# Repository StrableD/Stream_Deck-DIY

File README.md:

# Stream_Deck-DIY

Ich habe mir vorgenommen ein Stream Deck mit 15 Tasten selber zu bauen.
In diesem Repository will ich meine Reise dokumentieren und damit auch eine Anleitung für andere geben.

---

**Annotation:** For the English version, check [this section](#english-version).

## Ziele

- selbstgebautes Stream Deck mit 15 Tasten
- kompatibel mit Stream Deck Software und Alternativen
- günstiger als das Original

## Aktueller Stand

Aktuell sind wir in der Planungsphase.

Für weitere Informationen zur Planung und zukünftige Umsetzung schau dir die Dateien, welche in der [folgenden Sektion](#dateien) beschrieben werden, an.

## Dateien

Aufgeteilt sind die Dateien in Deutsch ([`de` Ordner](./de/)) und Englisch ([`en` Ordner](#english-version)).
Hierbei sind sie gleich benannt, damit man sie einfach vergleichen kann.

Hierbei gibt es folgende Dateien:

- `README.md`: Diese Datei, mit einer Übersicht über das Projekt ([englische Version](#english-version) in `en/README.md`)
- `planned.md`: Geplante Funktionen, Bauteile, Schaltplan, Aufbau
- `roadmap.md`: Geplanter Zeitplan für die Umsetzung
- `stream_deck-circuit`: Das KiCad Projekt mit Schaltplan und PCB-Layout

## English version

There is a english translation planned.
It can be found in the `en` folder.

## Credits

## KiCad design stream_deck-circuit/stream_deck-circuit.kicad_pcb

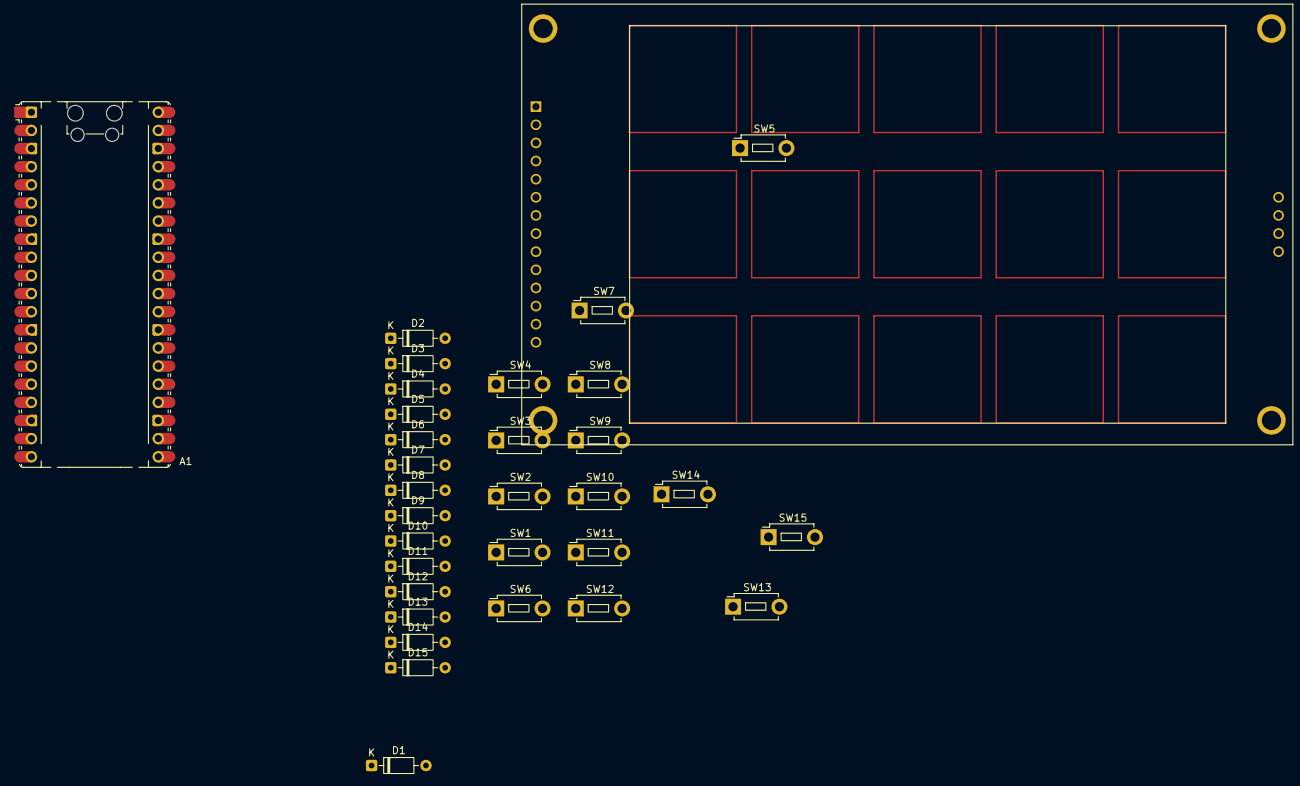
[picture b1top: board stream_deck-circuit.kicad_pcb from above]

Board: 2 copper layers, 32 parts (0 on the bottom side), 29 nets, no tracks yet.

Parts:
A1: RaspberryPi_Pico; RaspberryPi_Pico_Common_Unspecified
D1, D2, D3, D4, D5, D6, D7, D8, D9, D10, D11, D12, D13, D14, D15: 1N4148; D_DO-35_SOD27_P7.62mm_Horizontal
ST1: CR2019-MI5027
SW1, SW2, SW3, SW4, SW5, SW6, SW7, SW8, SW9, SW10, SW11, SW12, SW13, SW14, SW15: SW_MEC_5G; SW_PUSH_1P1T_6x3.5mm_H5.0_APEM_MJTP1250

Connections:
unnamed: A1.36 (3V3), ST1.1 (VCC)
unnamed: A1.5 (GPIO3), D1.1 (K), D6.1 (K), D11.1 (K)
unnamed: A1.6 (GPIO4), D2.1 (K), D7.1 (K), D12.1 (K)
unnamed: A1.7 (GPIO5), D3.1 (K), D8.1 (K), D13.1 (K)
unnamed: A1.9 (GPIO6), D4.1 (K), D9.1 (K), D14.1 (K)
unnamed: A1.10 (GPIO7), D5.1 (K), D10.1 (K), D15.1 (K)
unnamed: A1.21 (GPIO16), ST1.9 (SDO_(MISO))
unnamed: A1.22 (GPIO17), ST1.3 (CS)
unnamed: A1.24 (GPIO18), ST1.7 (SCK)
unnamed: A1.25 (GPIO19), ST1.6 (SDI_(MOSI))
unnamed: A1.26 (GPIO20), ST1.4 (RESET)
unnamed: A1.27 (GPIO21), ST1.8 (LED_(BL))
unnamed: A1.29 (GPIO22), ST1.5 (DC/RS)
unnamed: D1.2 (A), SW1.1 (A), SW1.2 (A)
unnamed: D2.2 (A), SW2.1 (A), SW2.2 (A)
unnamed: D3.2 (A), SW3.1 (A), SW3.2 (A)
unnamed: D4.2 (A), SW4.1 (A), SW4.2 (A)
unnamed: D5.2 (A), SW5.1 (A), SW5.2 (A)
unnamed: D6.2 (A), SW6.1 (A), SW6.2 (A)
unnamed: D7.2 (A), SW7.1 (A), SW7.2 (A)
unnamed: D8.2 (A), SW8.1 (A), SW8.2 (A)
unnamed: D9.2 (A), SW9.1 (A), SW9.2 (A)
unnamed: D10.2 (A), SW10.1 (A), SW10.2 (A)
unnamed: D11.2 (A), SW11.1 (A), SW11.2 (A)
unnamed: D12.2 (A), SW12.1 (A), SW12.2 (A)
unnamed: D13.2 (A), SW13.1 (A), SW13.2 (A)
unnamed: D14.2 (A), SW14.1 (A), SW14.2 (A)
unnamed: D15.2 (A), SW15.1 (A), SW15.2 (A)
unnamed: A1.3 (GND), A1.8 (GND), A1.13 (GND), A1.18 (GND), A1.23 (GND), A1.28 (GND), A1.38 (GND), ST1.2 (GND)

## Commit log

2026-04-07 Aktualisiere README.md und plane.md mit zusätzlichen Informationen und Formatierungen
2026-04-07 Füge .gitignore hinzu und aktualisiere README.md sowie planned.md mit neuen Informationen und Struktur
2026-04-08 Aktualisiere planned.md mit einer detaillierten Teileliste und Werkzeuganforderungen; füge roadmap.md hinzu, um den Projektverlauf zu skizzieren
2026-04-08 Add symbol library and lock files for stream deck circuit project
    - Created a new symbol library table for custom symbols in KiCad.
    - Added lock files for the PCB, project, and schematic to manage concurrent access.
2026-04-08 Update switch footprints in schematic and remove lock files
    - Changed the footprint of multiple button switches from "Button_Switch_SMD:SW_SPST_PTS645Sx43SMTR92" to "Button_Switch_THT:SW_PUSH_1P1T_6x3.5mm_H5.0_APEM_MJTP1250" in the schematic file.
    - Deleted lock files for the PCB, schematic, and project to ensure a clean working environment.
